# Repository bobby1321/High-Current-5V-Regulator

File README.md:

# High Current 5V DC Buck Converter Board
This board is a high current (8A) buck converter based around the TPS51386 for providing USB power to multiple devices from one board. Focused around working from a 4S Lithium Ion battery, it should work for any input voltage source from 10V-26V DC. The board also incorporates two INA219A PMICs for monitoring input & output power over I2C.

Also included in this repo is a small 4S Li-Ion battery voltage meter.

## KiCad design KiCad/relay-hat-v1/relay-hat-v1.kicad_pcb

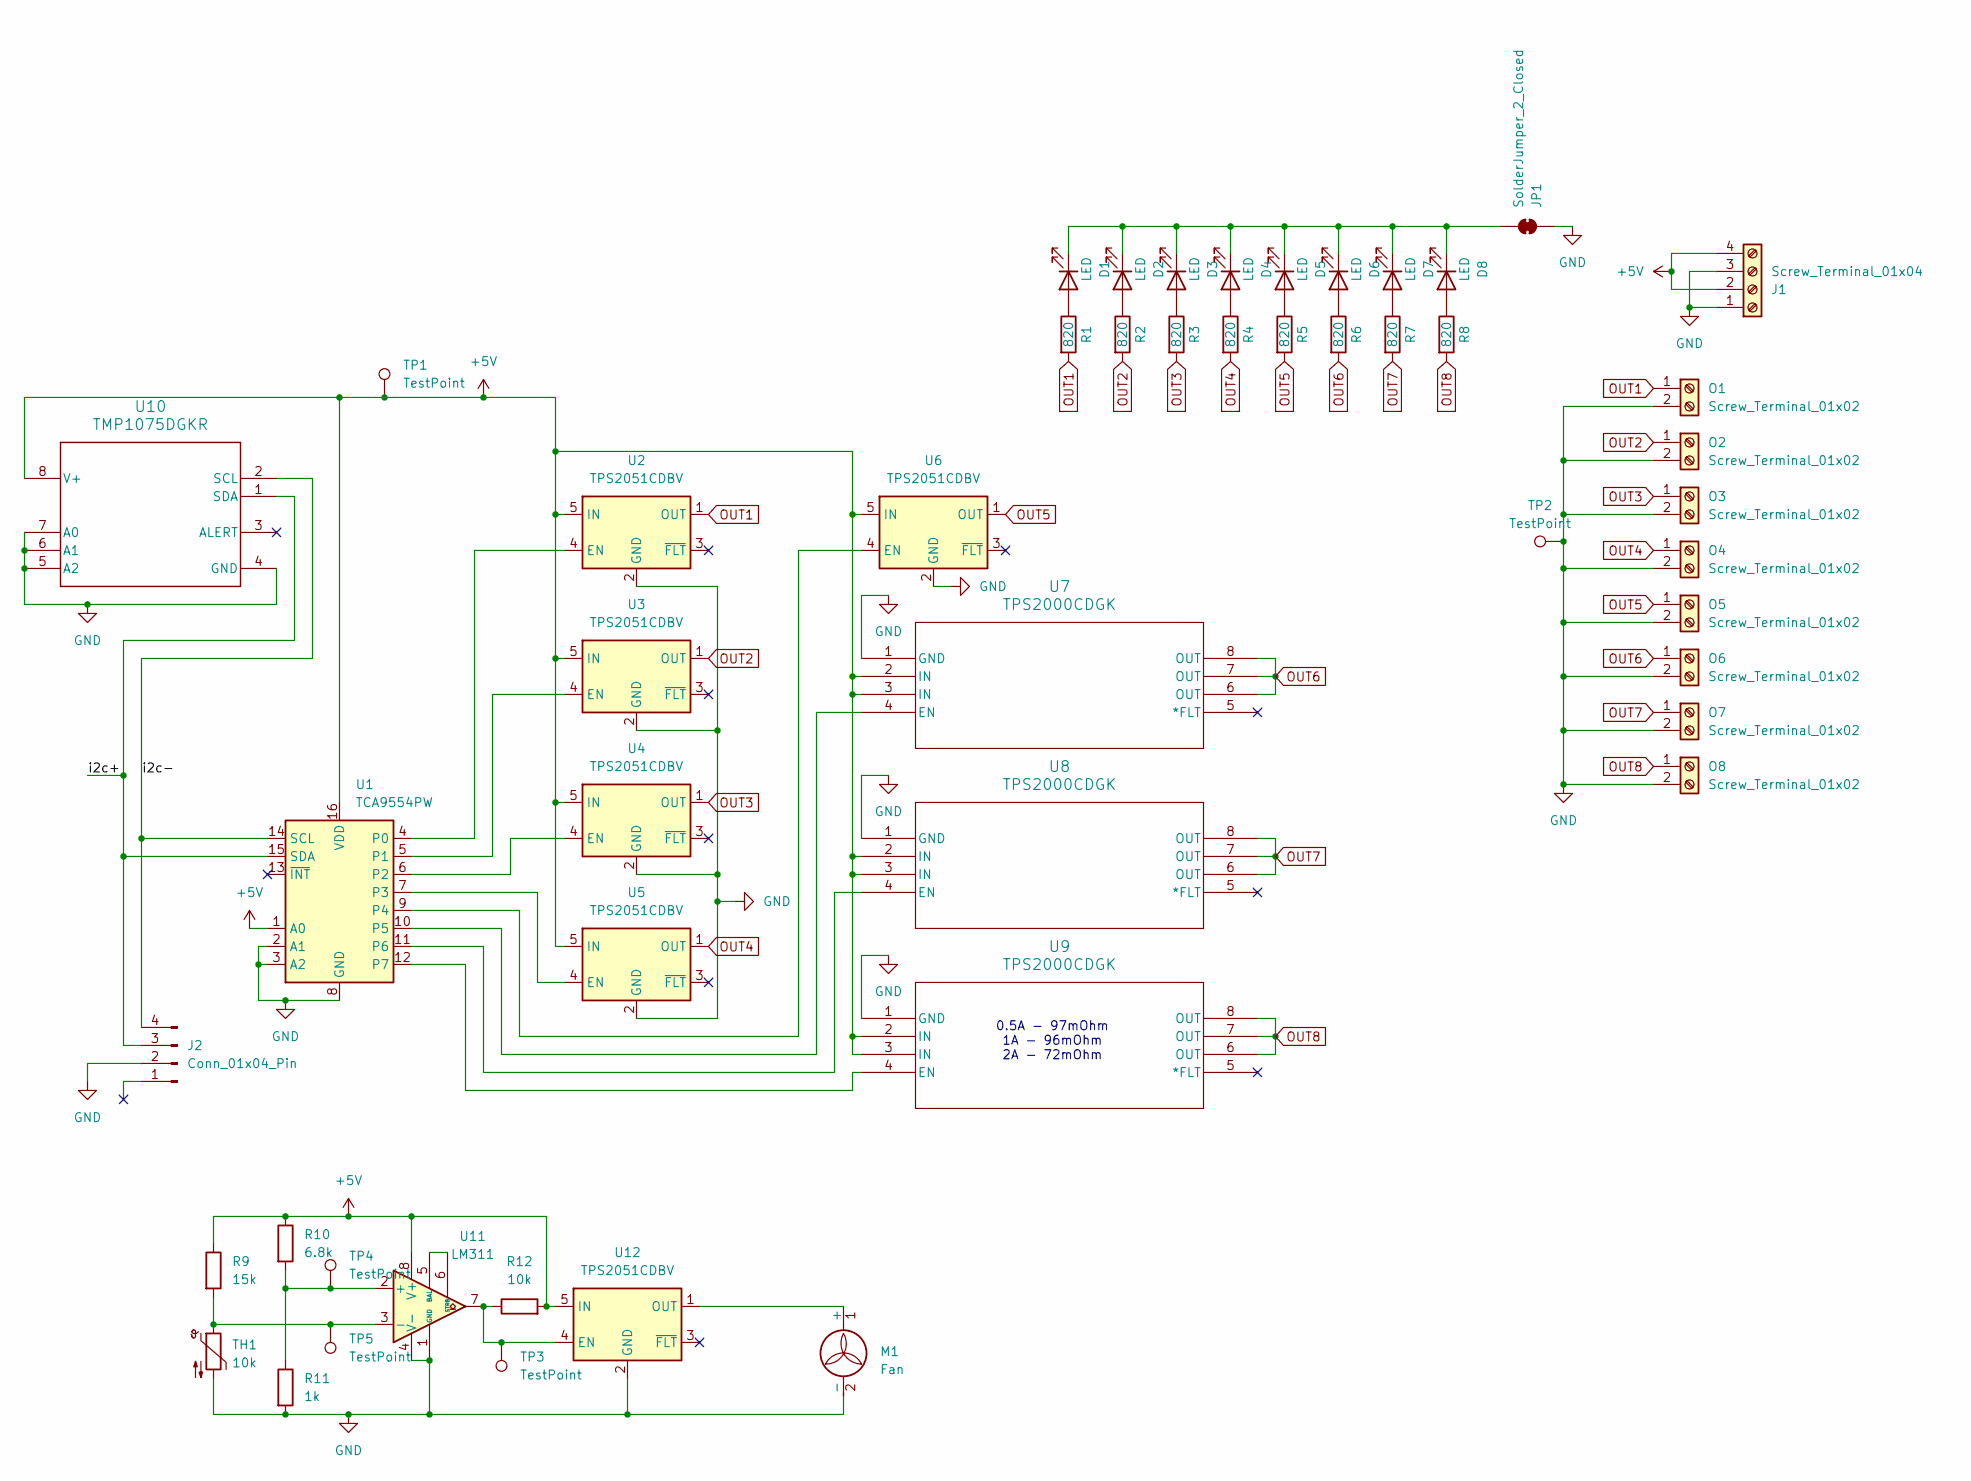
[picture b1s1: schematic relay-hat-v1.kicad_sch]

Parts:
D1, D2, D3, D4, D5, D6, D7, D8: LED; LED_0805_2012Metric_Pad1.15x1.40mm_HandSolder
J1: Screw_Terminal_01x04; TerminalBlock_Phoenix_MPT-0,5-4-2.54_1x04_P2.54mm_Horizontal
J2: Conn_01x04_Pin; PinHeader_1x04_P2.54mm_Vertical
JP1: SolderJumper_2_Closed; SolderJumper-2_P1.3mm_Open_TrianglePad1.0x1.5mm
M1: Fan; JST_XH_B2B-XH-A_1x02_P2.50mm_Vertical
O1, O2, O3, O4, O5, O6, O7, O8: Screw_Terminal_01x02; TerminalBlock_Phoenix_MPT-0,5-2-2.54_1x02_P2.54mm_Horizontal
R1, R2, R3, R4, R5, R6, R7, R8: 820; R_0805_2012Metric_Pad1.20x1.40mm_HandSolder
R9: 15k; R_0805_2012Metric_Pad1.20x1.40mm_HandSolder
R10: 6.8k; R_0805_2012Metric_Pad1.20x1.40mm_HandSolder
R11: 1k; R_0805_2012Metric_Pad1.20x1.40mm_HandSolder
R12: 10k; R_0805_2012Metric_Pad1.20x1.40mm_HandSolder
TH1: 10k; JST_XH_B2B-XH-A_1x02_P2.50mm_Vertical
TP1, TP2, TP3, TP4, TP5: TestPoint; TestPoint_Pad_D1.0mm
U1: TCA9554PW; TSSOP-16_4.4x5mm_P0.65mm
U2, U3, U4, U5, U6, U12: TPS2051CDBV; SOT-23-5
U7, U8, U9: TPS2000CDGK; DGK8
U10: TMP1075DGKR; DGK0008A_N
U11: LM311; SOIC-8_3.9x4.9mm_P1.27mm

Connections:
+5V: J1.2, J1.4, R9.1, R10.1, R12.2, TP1.1, U1.1 (A0), U1.16 (VDD), U2.5 (IN), U3.5 (IN), U4.5 (IN), U5.5 (IN), U6.5 (IN), U7.2 (IN), U7.3 (IN), U8.2 (IN), U8.3 (IN), U9.2 (IN), U9.3 (IN), U10.8 (V+), U11.8 (V+), U12.5 (IN)
/i2c+: J2.3, U1.15 (SDA), U10.1 (SDA)
/i2c-: J2.4, U1.14 (SCL), U10.2 (SCL)
GND: J1.1, J1.3, J2.2, JP1.2 (B), M1.2 (-), O1.2, O2.2, O3.2, O4.2, O5.2, O6.2, O7.2, O8.2, R11.2, TH1.2, TP2.1, U1.2 (A1), U1.3 (A2), U1.8 (GND), U2.2 (GND), U3.2 (GND), U4.2 (GND), U5.2 (GND), U6.2 (GND), U7.1 (GND), U8.1 (GND), U9.1 (GND), U10.4 (GND), U10.5 (A2), U10.6 (A1), U10.7 (A0), U11.1 (GND), U11.4 (V-), U12.2 (GND)
unnamed: D1.2 (A), R1.1
unnamed: D1.1 (K), D2.1 (K), D3.1 (K), D4.1 (K), D5.1 (K), D6.1 (K), D7.1 (K), D8.1 (K), JP1.1 (A)
unnamed: D2.2 (A), R2.1
unnamed: D3.2 (A), R3.1
unnamed: D4.2 (A), R4.1
unnamed: D5.2 (A), R5.1
unnamed: D6.2 (A), R6.1
unnamed: D7.2 (A), R7.1
unnamed: D8.2 (A), R8.1
unnamed: M1.1 (+), U12.1 (OUT)
unnamed: U1.4 (P0), U2.4 (EN)
unnamed: U1.5 (P1), U3.4 (EN)
unnamed: U1.6 (P2), U4.4 (EN)
unnamed: U1.7 (P3), U5.4 (EN)
unnamed: U1.9 (P4), U6.4 (EN)
unnamed: U1.10 (P5), U7.4 (EN)
unnamed: U1.11 (P6), U8.4 (EN)
unnamed: U1.12 (P7), U9.4 (EN)
unnamed: R10.2, R11.1, TP4.1, U11.2 (+)
unnamed: R9.2, TH1.1, TP5.1, U11.3 (-)
unnamed: U11.5 (BAL), U11.6 (STRB)
unnamed: R12.1, TP3.1, U11.7, U12.4 (EN)
OUT1: O1.1, R1.2, U2.1 (OUT)
OUT2: O2.1, R2.2, U3.1 (OUT)
OUT3: O3.1, R3.2, U4.1 (OUT)
OUT4: O4.1, R4.2, U5.1 (OUT)
OUT5: O5.1, R5.2, U6.1 (OUT)
OUT6: O6.1, R6.2, U7.6 (OUT), U7.7 (OUT), U7.8 (OUT)
OUT7: O7.1, R7.2, U8.6 (OUT), U8.7 (OUT), U8.8 (OUT)
OUT8: O8.1, R8.2, U9.6 (OUT), U9.7 (OUT), U9.8 (OUT)

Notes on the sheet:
0.5A - 97mOhm 1A - 96mOhm 2A - 72mOhm

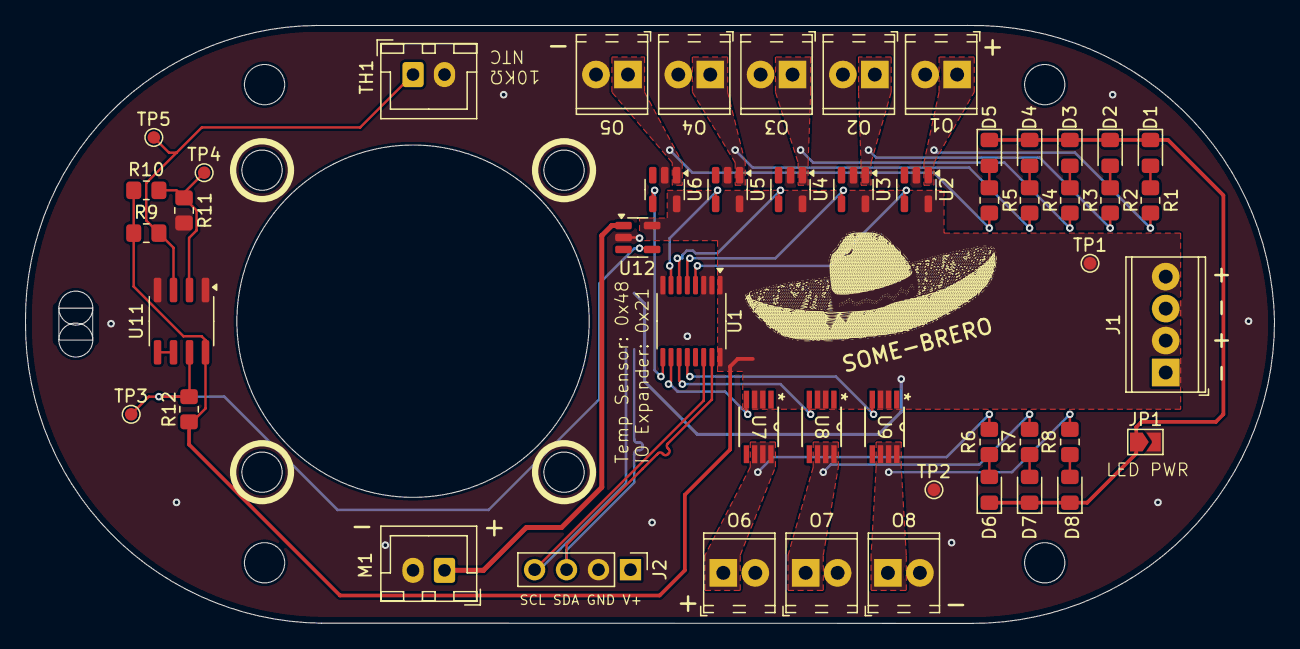
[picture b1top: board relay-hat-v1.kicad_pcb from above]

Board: 2 copper layers, 99.3 x 47.5 mm, 50 parts (1 on the bottom side), 34 nets.

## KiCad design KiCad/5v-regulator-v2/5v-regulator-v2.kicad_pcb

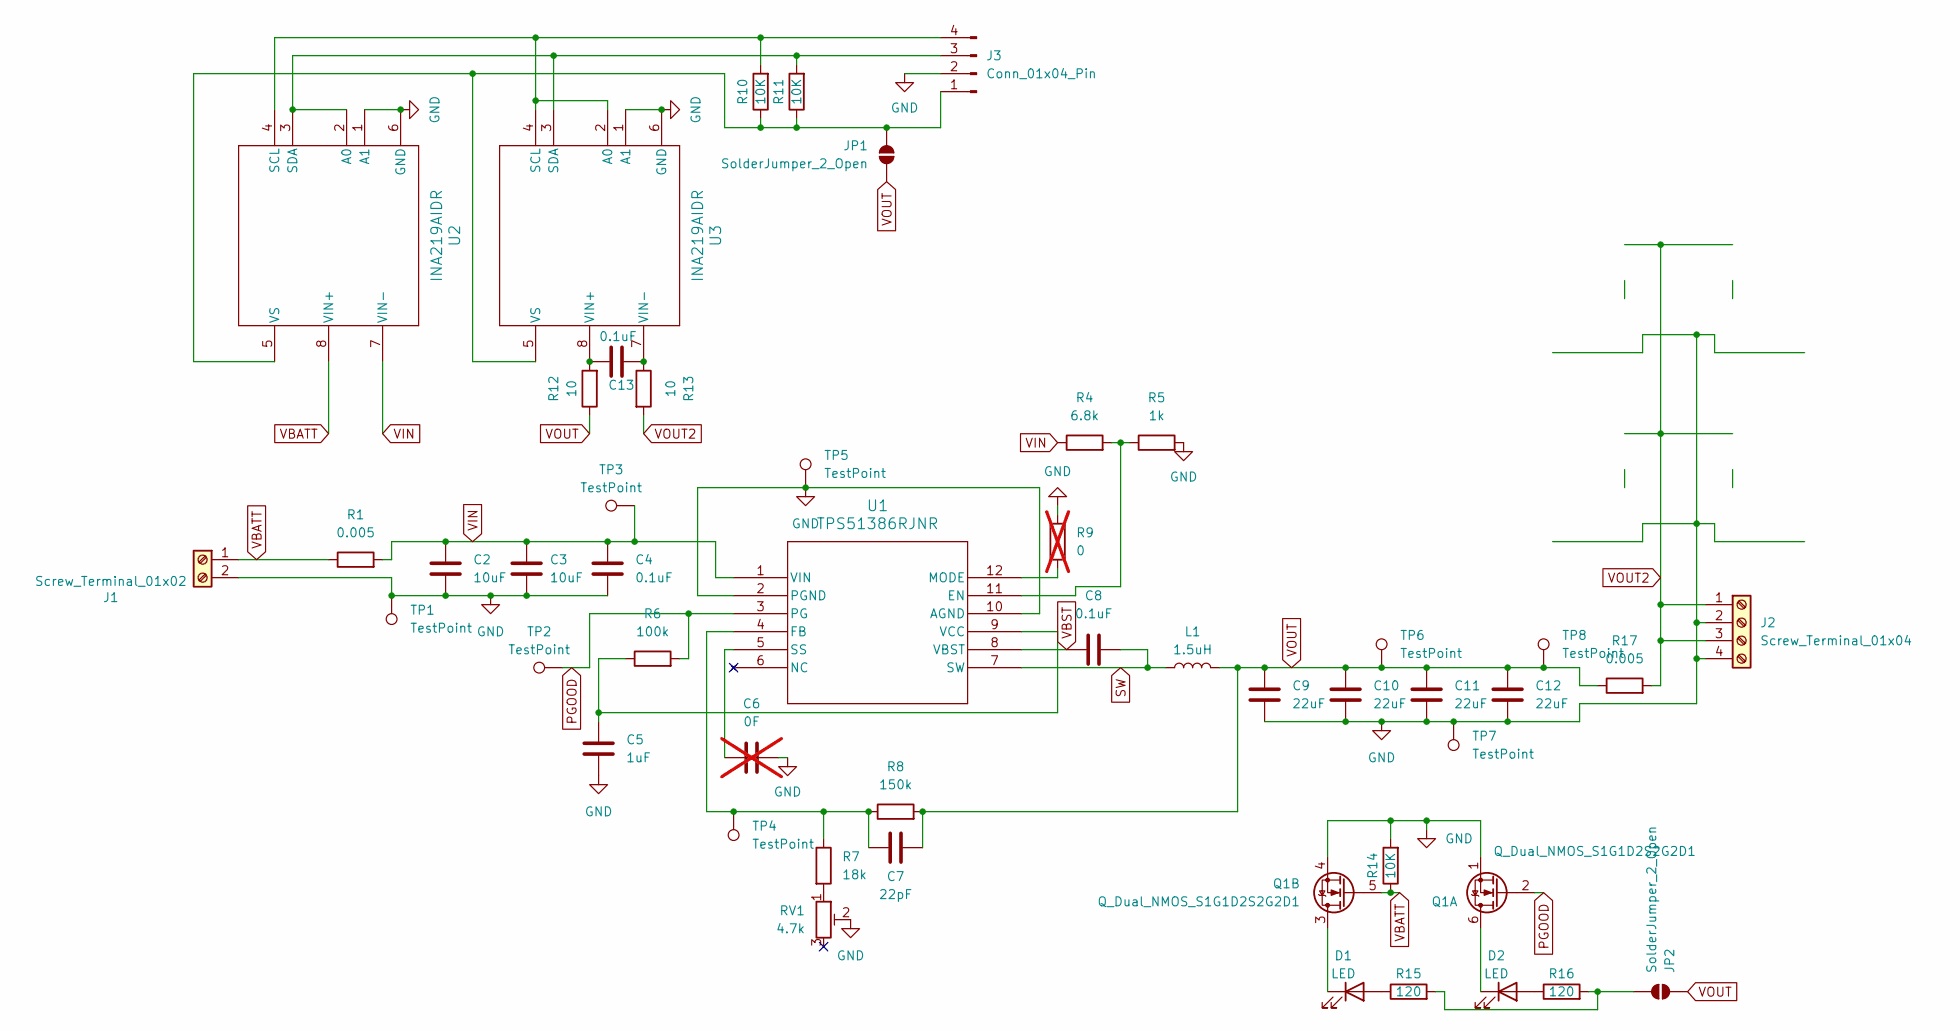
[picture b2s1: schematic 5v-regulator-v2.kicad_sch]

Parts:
C2, C3: 10uF; C_1206_3216Metric_Pad1.33x1.80mm_HandSolder
C4, C8, C13: 0.1uF; C_1206_3216Metric_Pad1.33x1.80mm_HandSolder
C5: 1uF; C_1206_3216Metric_Pad1.33x1.80mm_HandSolder
C6: 0F; C_1206_3216Metric_Pad1.33x1.80mm_HandSolder; not fitted
C7: 22pF; C_1206_3216Metric_Pad1.33x1.80mm_HandSolder
C9, C10, C11, C12: 22uF; C_1206_3216Metric_Pad1.33x1.80mm_HandSolder
D1, D2: LED; LED_0805_2012Metric_Pad1.15x1.40mm_HandSolder
J1: Screw_Terminal_01x02; TerminalBlock_Xinya_XY308-2.54-2P_1x02_P2.54mm_Horizontal
J2: Screw_Terminal_01x04; TerminalBlock_Xinya_XY308-2.54-4P_1x04_P2.54mm_Horizontal
J3: Conn_01x04_Pin; PinHeader_1x04_P2.54mm_Vertical
JP1, JP2: SolderJumper_2_Open; SolderJumper-2_P1.3mm_Open_TrianglePad1.0x1.5mm
L1: 1.5uH; L_Panasonic_ETQP4M---KVK
Q1: Q_Dual_NMOS_S1G1D2S2G2D1; SOT-363_SC-70-6_Handsoldering
R1, R17: 0.005; R_1206_3216Metric_Pad1.30x1.75mm_HandSolder
R4: 6.8k; R_0805_2012Metric_Pad1.20x1.40mm_HandSolder
R5: 1k; R_0805_2012Metric_Pad1.20x1.40mm_HandSolder
R6: 100k; R_1206_3216Metric_Pad1.30x1.75mm_HandSolder
R7: 18k; R_1206_3216Metric_Pad1.30x1.75mm_HandSolder
R8: 150k; R_1206_3216Metric_Pad1.30x1.75mm_HandSolder
R9: 0; R_1206_3216Metric_Pad1.30x1.75mm_HandSolder; not fitted
R10, R11, R14: 10K; R_0805_2012Metric_Pad1.20x1.40mm_HandSolder
R12, R13: 10; R_1206_3216Metric_Pad1.30x1.75mm_HandSolder
R15, R16: 120; R_0805_2012Metric_Pad1.20x1.40mm_HandSolder
RV1: 4.7k; Potentiometer_Bourns_TC33X_Vertical
TP1, TP2, TP3, TP4, TP5, TP6, TP7: TestPoint; TestPoint_Pad_D2.0mm
TP8: TestPoint; usb_symbol
U1: TPS51386RJNR; VQFN-HR12_RJN_TEX
U2, U3: INA219AIDR; SOT-23-8

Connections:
GND: C2.2, C3.2, C4.2, C5.2, C6.2, C9.2, C10.2, C11.2, C12.2, J1.2, J2.2, J2.4, J3.2, Q1.1 (S), Q1.4 (S), R5.2, R9.2, R14.2, RV1.2, TP1.1, TP5.1, TP7.1, U1.2 (PGND), U1.10 (AGND), U2.1 (A1), U2.6 (GND), U3.1 (A1), U3.6 (GND)
unnamed: D1.2 (A), R15.1
unnamed: D1.1 (K), Q1.3 (D)
unnamed: D2.2 (A), R16.1
unnamed: D2.1 (K), Q1.6 (D)
unnamed: J3.1, JP1.2 (B), R10.1, R11.1, U2.5 (VS), U3.5 (VS)
unnamed: J3.3, R11.2, U2.2 (A0), U2.3 (SDA), U3.3 (SDA)
unnamed: J3.4, R10.2, U2.4 (SCL), U3.2 (A0), U3.4 (SCL)
unnamed: JP2.1 (A), R15.2, R16.2
unnamed: R7.2, RV1.1
unnamed: R4.2, R5.1, U1.11 (EN)
unnamed: C7.2, R7.1, R8.1, TP4.1, U1.4 (FB)
unnamed: R9.1, U1.12 (MODE)
unnamed: C6.1, U1.5 (SS)
unnamed: C5.1, R6.1, U1.9 (VCC)
unnamed: C13.2, R12.2, U3.8 (VIN+)
unnamed: C13.1, R13.1, U3.7 (VIN-)
PGOOD: Q1.2 (G), R6.2, TP2.1, U1.3 (PG)
SW: C8.2, L1.1, U1.7 (SW)
VBATT: J1.1, Q1.5 (G), R1.1, R14.1, U2.8 (VIN+)
VBST: C8.1, U1.8 (VBST)
VIN: C2.1, C3.1, C4.1, R1.2, R4.1, TP3.1, U1.1 (VIN), U2.7 (VIN-)
VOUT: C7.1, C9.1, C10.1, C11.1, C12.1, JP1.1 (A), JP2.2 (B), L1.2, R8.2, R12.1, R17.1, TP6.1, TP8.1
VOUT2: J2.1, J2.3, R13.2, R17.2

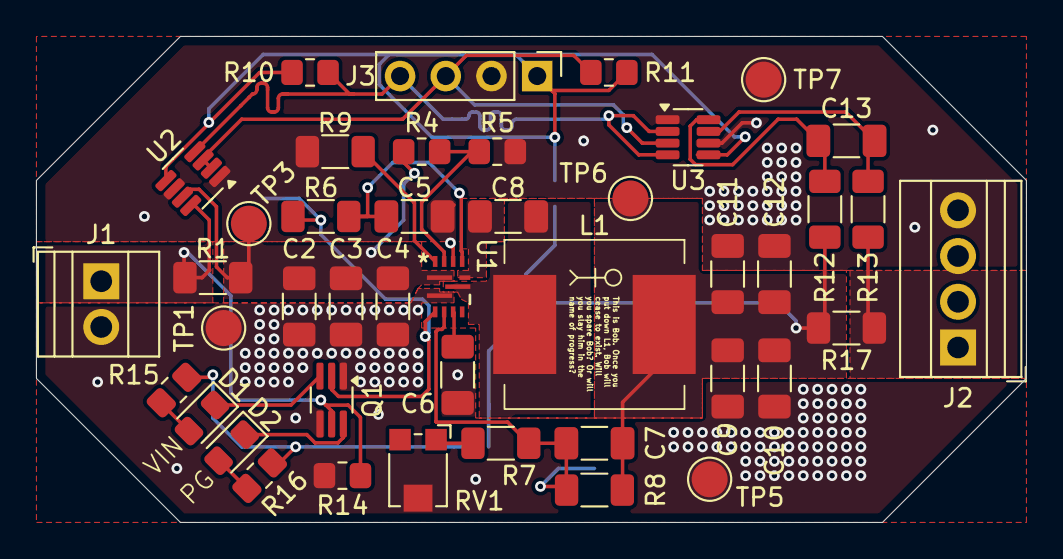
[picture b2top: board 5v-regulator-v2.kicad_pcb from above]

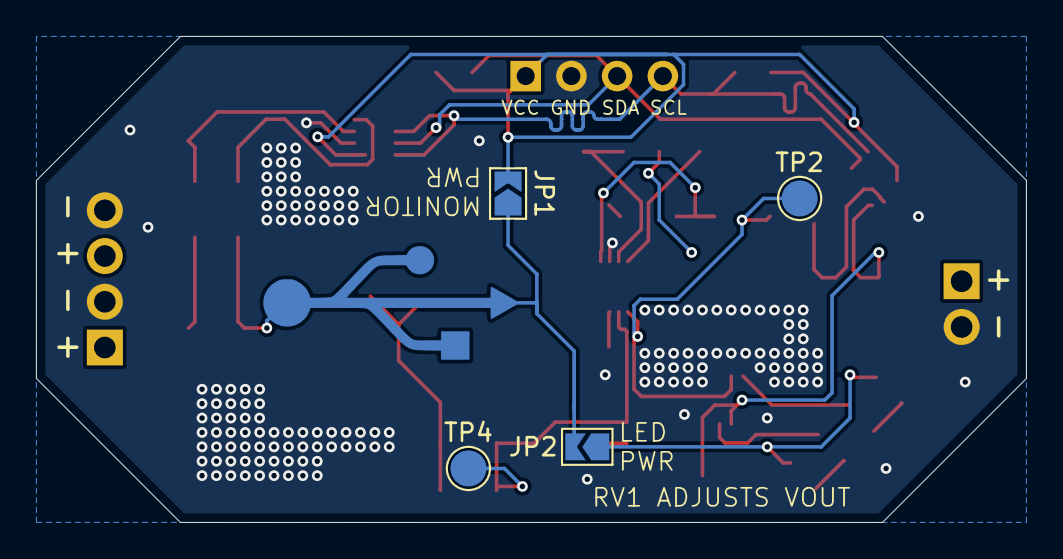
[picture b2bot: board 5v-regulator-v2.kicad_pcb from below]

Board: 2 copper layers, 55.0 x 27.0 mm, 48 parts (5 on the bottom side), 24 nets.

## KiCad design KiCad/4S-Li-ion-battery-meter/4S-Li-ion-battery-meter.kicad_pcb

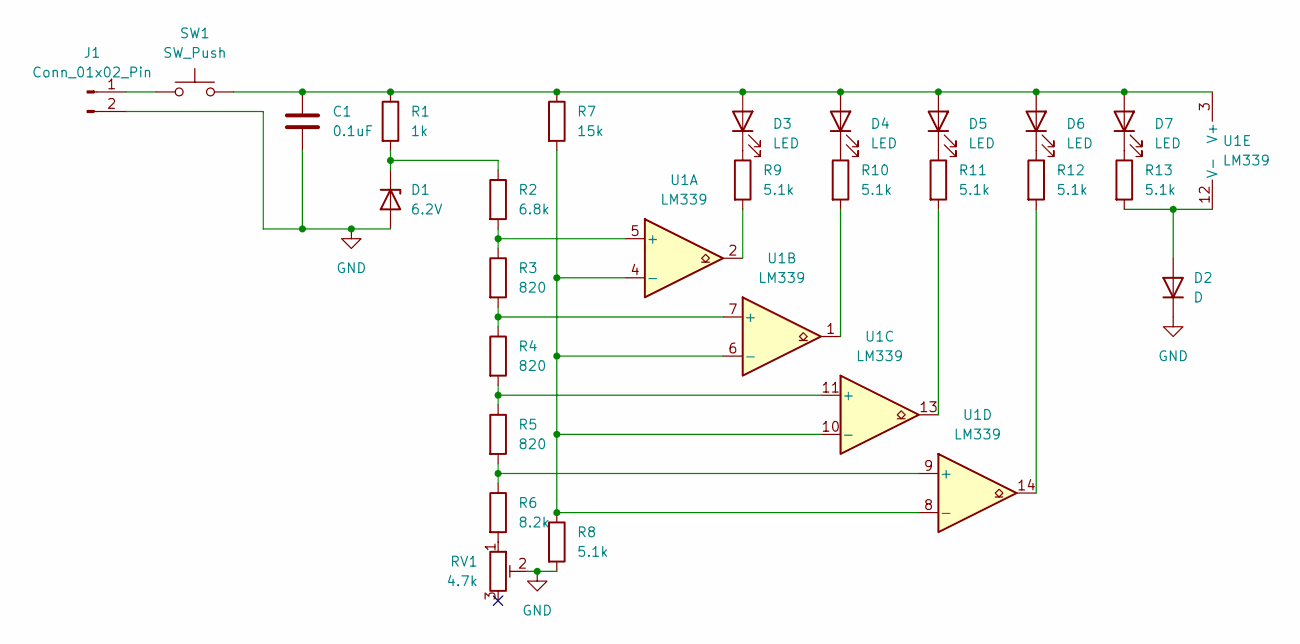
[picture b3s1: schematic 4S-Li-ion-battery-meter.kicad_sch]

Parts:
C1: 0.1uF; C_1206_3216Metric_Pad1.33x1.80mm_HandSolder
D1: 6.2V; D_SOD-123
D2: D; D_SOD-123
D3, D4, D5, D6, D7: LED; LED_0805_2012Metric_Pad1.15x1.40mm_HandSolder
J1: Conn_01x02_Pin; PinHeader_1x02_P2.54mm_Vertical
R1: 1k; R_0805_2012Metric_Pad1.20x1.40mm_HandSolder
R2: 6.8k; R_0805_2012Metric_Pad1.20x1.40mm_HandSolder
R3, R4, R5: 820; R_0805_2012Metric_Pad1.20x1.40mm_HandSolder
R6: 8.2k; R_0805_2012Metric_Pad1.20x1.40mm_HandSolder
R7: 15k; R_0805_2012Metric_Pad1.20x1.40mm_HandSolder
R8, R9, R10, R11, R12, R13: 5.1k; R_0805_2012Metric_Pad1.20x1.40mm_HandSolder
RV1: 4.7k; Potentiometer_Bourns_TC33X_Vertical
SW1: SW_Push; SW_Push_1P1T_NO_6x6mm_H9.5mm
U1: LM339; SSOP-14_5.3x6.2mm_P0.65mm

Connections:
GND: C1.2, D1.2 (A), D2.1 (K), J1.2, R8.2, RV1.2
unnamed: D1.1 (K), R1.2, R2.1
unnamed: D2.2 (A), R13.2, U1.12 (V-)
unnamed: C1.1, D3.2 (A), D4.2 (A), D5.2 (A), D6.2 (A), D7.2 (A), R1.1, R7.1, SW1.2, U1.3 (V+)
unnamed: D3.1 (K), R9.1
unnamed: D4.1 (K), R10.1
unnamed: D5.1 (K), R11.1
unnamed: D6.1 (K), R12.1
unnamed: D7.1 (K), R13.1
unnamed: J1.1, SW1.1
unnamed: R6.2, RV1.1
unnamed: R9.2, U1.2
unnamed: R10.2, U1.1
unnamed: R11.2, U1.13
unnamed: R12.2, U1.14
unnamed: R2.2, R3.1, U1.5 (+)
unnamed: R7.2, R8.1, U1.4 (-), U1.6 (-), U1.8 (-), U1.10 (-)
unnamed: R3.2, R4.1, U1.7 (+)
unnamed: R4.2, R5.1, U1.11 (+)
unnamed: R5.2, R6.1, U1.9 (+)

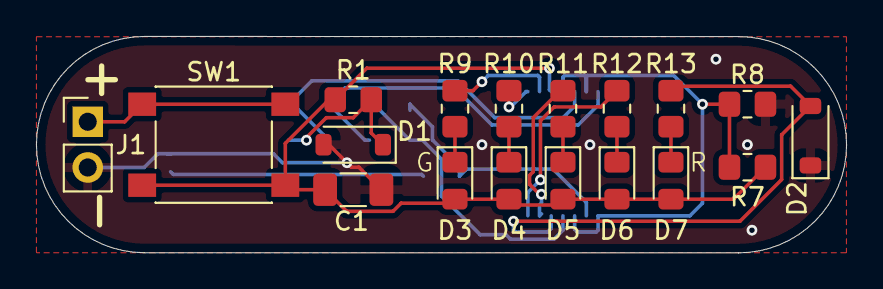
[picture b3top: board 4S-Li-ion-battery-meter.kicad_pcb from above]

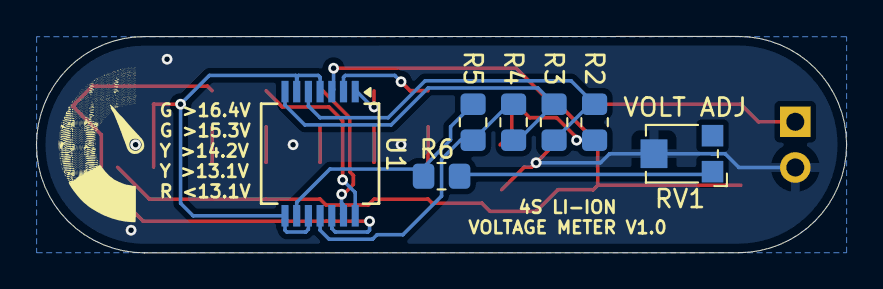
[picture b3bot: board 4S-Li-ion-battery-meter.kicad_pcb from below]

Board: 2 copper layers, 45.0 x 12.0 mm, 25 parts (7 on the bottom side), 20 nets.

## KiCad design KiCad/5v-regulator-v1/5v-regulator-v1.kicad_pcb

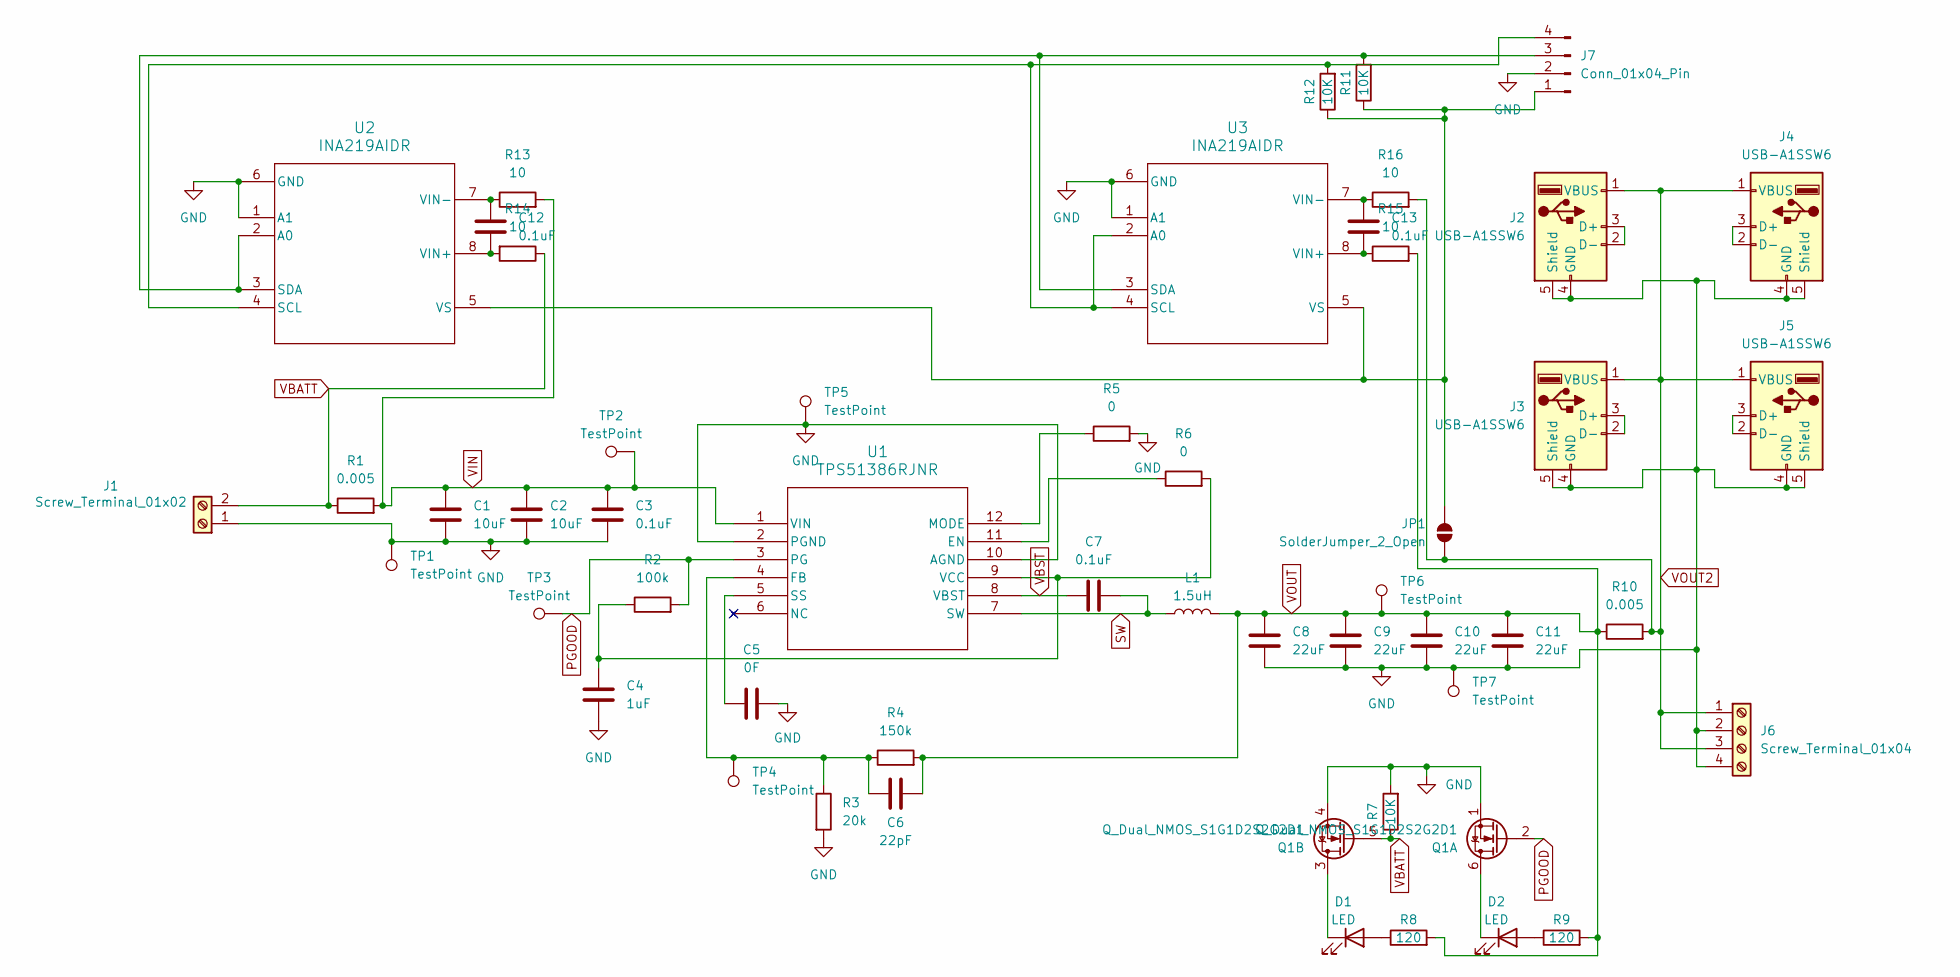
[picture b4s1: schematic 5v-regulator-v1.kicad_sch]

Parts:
C1, C2: 10uF; C_1206_3216Metric_Pad1.33x1.80mm_HandSolder
C3, C7, C12, C13: 0.1uF; C_1206_3216Metric_Pad1.33x1.80mm_HandSolder
C4: 1uF; C_1206_3216Metric_Pad1.33x1.80mm_HandSolder
C5: 0F; C_1206_3216Metric_Pad1.33x1.80mm_HandSolder
C6: 22pF; C_1206_3216Metric_Pad1.33x1.80mm_HandSolder
C8, C9, C10, C11: 22uF; C_1206_3216Metric_Pad1.33x1.80mm_HandSolder
D1, D2: LED; LED_0805_2012Metric_Pad1.15x1.40mm_HandSolder
J1: Screw_Terminal_01x02; TerminalBlock_Xinya_XY308-2.54-2P_1x02_P2.54mm_Horizontal
J2, J3, J4, J5: USB-A1SSW6; USB_A_Wuerth_614004134726_Horizontal; PARTREV A
J6: Screw_Terminal_01x04; TerminalBlock_Xinya_XY308-2.54-4P_1x04_P2.54mm_Horizontal
J7: Conn_01x04_Pin; PinHeader_1x04_P2.54mm_Vertical
JP1: SolderJumper_2_Open; SolderJumper-2_P1.3mm_Open_TrianglePad1.0x1.5mm
L1: 1.5uH; IND_WE-LHMI_8030_WRE
Q1: Q_Dual_NMOS_S1G1D2S2G2D1; SOT-363_SC-70-6_Handsoldering
R1, R10: 0.005; R_1206_3216Metric_Pad1.30x1.75mm_HandSolder
R2: 100k; R_1206_3216Metric_Pad1.30x1.75mm_HandSolder
R3: 20k; R_1206_3216Metric_Pad1.30x1.75mm_HandSolder
R4: 150k; R_1206_3216Metric_Pad1.30x1.75mm_HandSolder
R5, R6: 0; R_1206_3216Metric_Pad1.30x1.75mm_HandSolder
R7, R11, R12: 10K; R_0805_2012Metric_Pad1.20x1.40mm_HandSolder
R8, R9: 120; R_0805_2012Metric_Pad1.20x1.40mm_HandSolder
R13, R14, R15, R16: 10; R_1206_3216Metric_Pad1.30x1.75mm_HandSolder
TP1, TP2, TP3, TP4, TP5, TP6, TP7: TestPoint; TestPoint_Pad_D2.0mm
U1: TPS51386RJNR; VQFN-HR12_RJN_TEX
U2, U3: INA219AIDR; SOIC-8_3.9x4.9mm_P1.27mm

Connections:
GND: C1.2, C2.2, C3.2, C4.2, C5.2, C8.2, C9.2, C10.2, C11.2, J1.1, J2.4 (GND), J2.5 (Shield), J3.4 (GND), J3.5 (Shield), J4.4 (GND), J4.5 (Shield), J5.4 (GND), J5.5 (Shield), J6.2, J6.4, J7.2, Q1.1 (S), Q1.4 (S), R3.2, R5.2, R7.2, TP1.1, TP5.1, TP7.1, U1.2 (PGND), U1.10 (AGND), U2.1 (A1), U2.6 (GND), U3.1 (A1), U3.6 (GND)
unnamed: D1.2 (A), R8.1
unnamed: D1.1 (K), Q1.3 (D)
unnamed: D2.2 (A), R9.1
unnamed: D2.1 (K), Q1.6 (D)
unnamed: J2.2 (D-), J2.3 (D+)
unnamed: J3.2 (D-), J3.3 (D+)
unnamed: J4.2 (D-), J4.3 (D+)
unnamed: J5.2 (D-), J5.3 (D+)
unnamed: J7.1, JP1.2 (B), R11.1, R12.1, U2.5 (VS), U3.5 (VS)
unnamed: J7.3, R11.2, U2.2 (A0), U2.3 (SDA), U3.3 (SDA)
unnamed: J7.4, R12.2, U2.4 (SCL), U3.2 (A0), U3.4 (SCL)
unnamed: R6.1, U1.11 (EN)
unnamed: C6.2, R3.1, R4.1, TP4.1, U1.4 (FB)
unnamed: R5.1, U1.12 (MODE)
unnamed: C5.1, U1.5 (SS)
unnamed: C4.1, R2.1, R6.2, U1.9 (VCC)
unnamed: C12.2, R14.2, U2.8 (VIN+)
unnamed: C12.1, R13.1, U2.7 (VIN-)
unnamed: C13.2, R15.1, U3.8 (VIN+)
unnamed: C13.1, R16.1, U3.7 (VIN-)
PGOOD: Q1.2 (G), R2.2, TP3.1, U1.3 (PG)
SW: C7.2, L1.1, U1.7 (SW)
VBATT: J1.2, Q1.5 (G), R1.1, R7.1, R14.1
VBST: C7.1, U1.8 (VBST)
VIN: C1.1, C2.1, C3.1, R1.2, R13.2, TP2.1, U1.1 (VIN)
VOUT: C6.1, C8.1, C9.1, C10.1, C11.1, L1.2, R4.2, R8.2, R9.2, R10.1, R15.2, TP6.1
VOUT2: J2.1 (VBUS), J3.1 (VBUS), J4.1 (VBUS), J5.1 (VBUS), J6.1, J6.3, JP1.1 (A), R10.2, R16.2

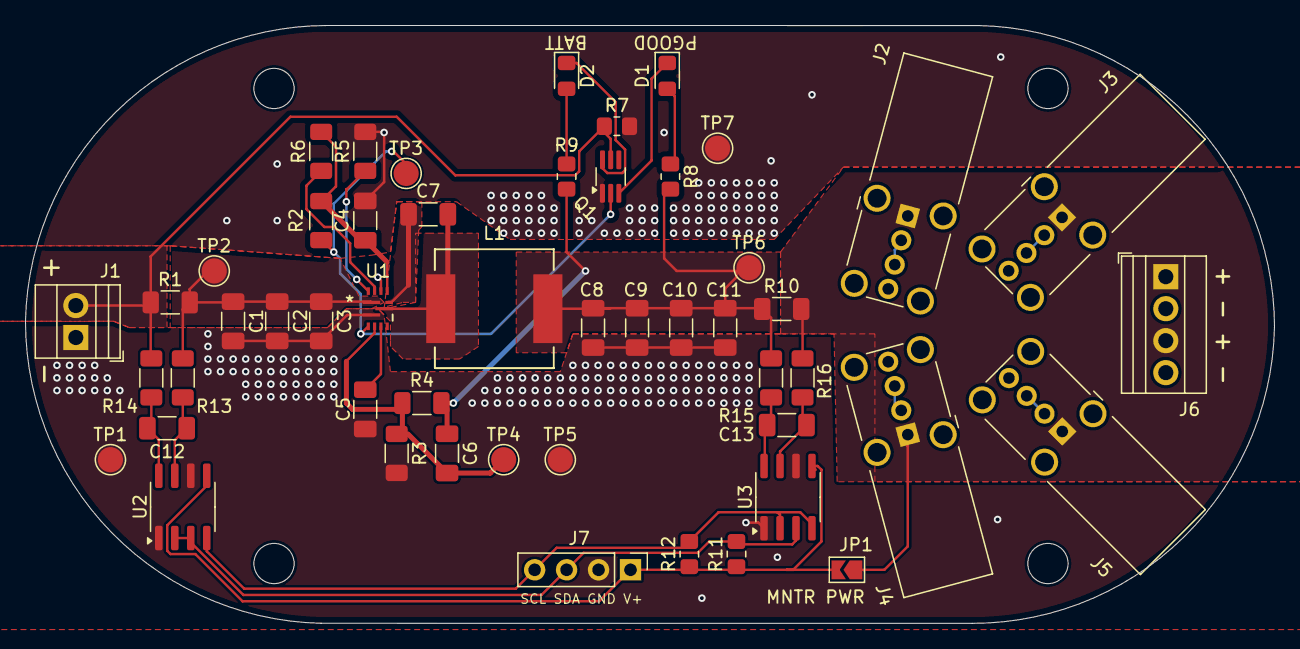
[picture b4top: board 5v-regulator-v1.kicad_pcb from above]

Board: 2 copper layers, 99.3 x 47.5 mm, 51 parts (0 on the bottom side), 28 nets.

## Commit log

2024-08-31 Updated PCB design
2024-08-31 Changed resistor values
2024-09-02 Blaine review
2024-09-06 Updated 5V reg and added battery meter
2024-09-08 Sent to production!
2024-09-10 Updating pictures
2024-09-10 Moved LTSpice files into their own folder
2024-09-21 Fixed errors (missing enable & overlapping trace)
    I should really RTFM and run the DRC...
2024-09-21 Added solder pad for LEDs
2024-09-21 v2 smaller board
2024-09-22 Uploading test data
2024-09-29 Added relay hats!
    Version 1 & version 2 have different version hats, but the versions are not compatible between version 1 and version 2 or vice versa
2024-09-29 Updated some silkscreen
2024-11-14 Test code and changed diode for resistor
    The diode after the op-amp on the relay board is now a 10K pullup resistor
2024-11-22 Updated some code and micro-some-brero
2025-01-10 Increased pitch of terminal blocks to fit ferrules
2025-01-11 Added input fuse and switched to stacked USBs
2025-02-14 Updated battery meter with 2S values
    Need to figure out a good way to automatically calculate resistor values based on input voltages...
